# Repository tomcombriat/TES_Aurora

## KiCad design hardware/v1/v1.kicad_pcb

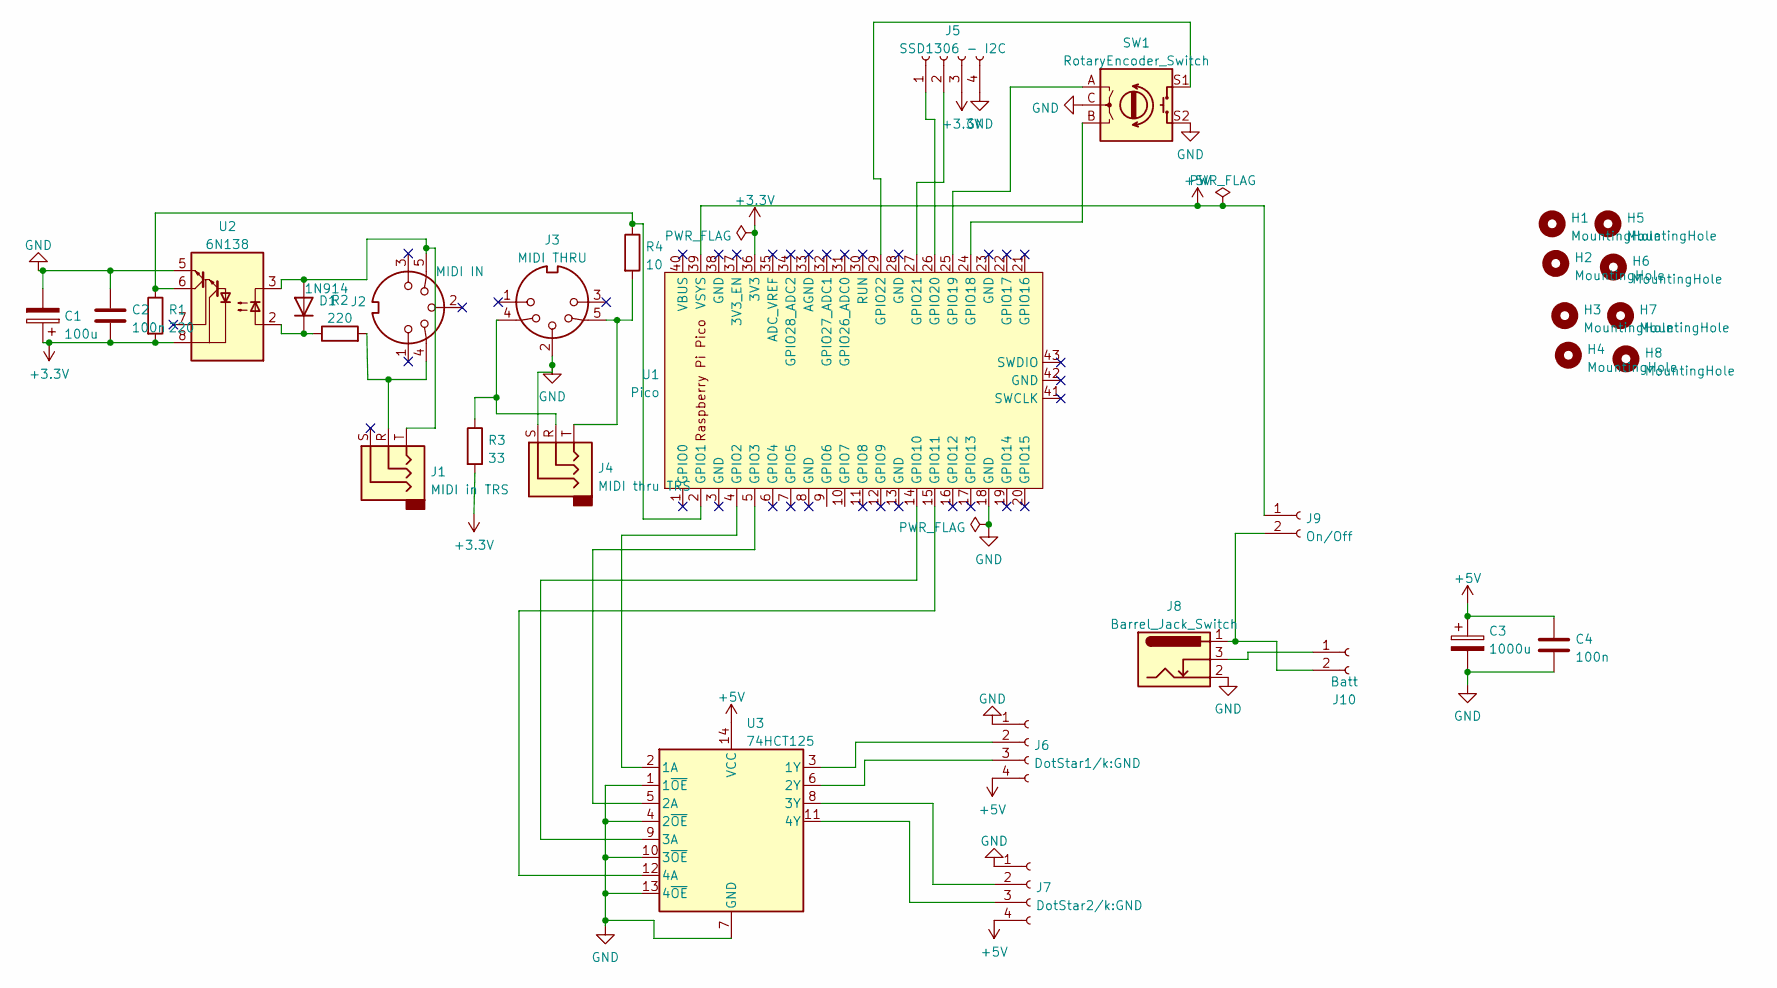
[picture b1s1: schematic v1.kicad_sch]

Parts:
C1: 100u; CP_Radial_D7.5mm_P2.50mm
C2, C4: 100n; C_Axial_L3.8mm_D2.6mm_P7.50mm_Horizontal
C3: 1000u; CP_Radial_D10.0mm_P5.00mm
D1: 1N914; D_DO-34_SOD68_P7.62mm_Horizontal
H1, H2, H3, H4, H5, H6, H7, H8: MountingHole; MountingHole_3.2mm_M3
J1: MIDI in TRS; PJ-320B
J2: MIDI IN; DS-5 MIDI_Wide
J3: MIDI THRU; DS-5 MIDI_Wide
J4: MIDI thru TRS; PJ-320B
J5: SSD1306 - I2C; JST_EH_B4B-EH-A_1x04_P2.50mm_Vertical
J6: DotStar1/k:GND; JST_PH_S4B-PH-K_1x04_P2.00mm_Horizontal
J7: DotStar2/k:GND; JST_PH_S4B-PH-K_1x04_P2.00mm_Horizontal
J8: Barrel_Jack_Switch; BarrelJack_CUI_PJ-102AH_Horizontal
J9: On/Off; JST_XH_B2B-XH-A_1x02_P2.50mm_Vertical
J10: Batt; JST_XH_B2B-XH-A_1x02_P2.50mm_Vertical
R1, R2: 220; R_Axial_DIN0207_L6.3mm_D2.5mm_P7.62mm_Horizontal
R3: 33; R_Axial_DIN0207_L6.3mm_D2.5mm_P7.62mm_Horizontal
R4: 10; R_Axial_DIN0207_L6.3mm_D2.5mm_P7.62mm_Horizontal
SW1: RotaryEncoder_Switch; RotaryEncoder_Alps_EC12E-Switch_Vertical_H20mm
U1: Pico; RPi_Pico_TH
U2: 6N138; DIP-8_W7.62mm_Socket
U3: 74HCT125; SOIC-14_3.9x8.7mm_P1.27mm

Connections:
+3.3V: C1.1, C2.2, J5.3, R1.2, R3.2, U1.36 (3V3), U2.8 (VCC)
+5V: C3.1, C4.2, J6.4, J7.4, J9.1, U1.39 (VSYS), U3.14 (VCC)
GND: C1.2, C2.1, C3.2, C4.1, J3.2, J4.S, J5.4, J6.1, J7.1, J8.2, SW1.C, SW1.S2, U1.18 (GND), U2.5 (GND), U3.1 (1~OE), U3.4 (2~OE), U3.7 (GND), U3.10 (3~OE), U3.13 (4~OE)
unnamed: D1.1 (K), R2.1, U2.2 (C1)
unnamed: D1.2 (A), J1.T, J2.5, U2.3 (C2)
unnamed: J1.R, J2.4, R2.2
unnamed: J3.4, J4.R, R3.1
unnamed: J3.5, J4.T, R4.2
unnamed: J6.2, U3.3 (1Y)
unnamed: J6.3, U3.6 (2Y)
unnamed: J7.2, U3.8 (3Y)
unnamed: J7.3, U3.11 (4Y)
unnamed: J8.3, J10.1
unnamed: J8.1, J9.2, J10.2
unnamed: R1.1, R4.1, U1.2 (GPIO1), U2.6 (VO2)
unnamed: U1.4 (GPIO2), U3.2 (1A)
unnamed: U1.5 (GPIO3), U3.5 (2A)
unnamed: U1.14 (GPIO10), U3.9 (3A)
unnamed: U1.15 (GPIO11), U3.12 (4A)
unnamed: SW1.B, U1.24 (GPIO18)
unnamed: SW1.A, U1.25 (GPIO19)
unnamed: J5.1, U1.26 (GPIO20)
unnamed: J5.2, U1.27 (GPIO21)
unnamed: SW1.S1, U1.29 (GPIO22)

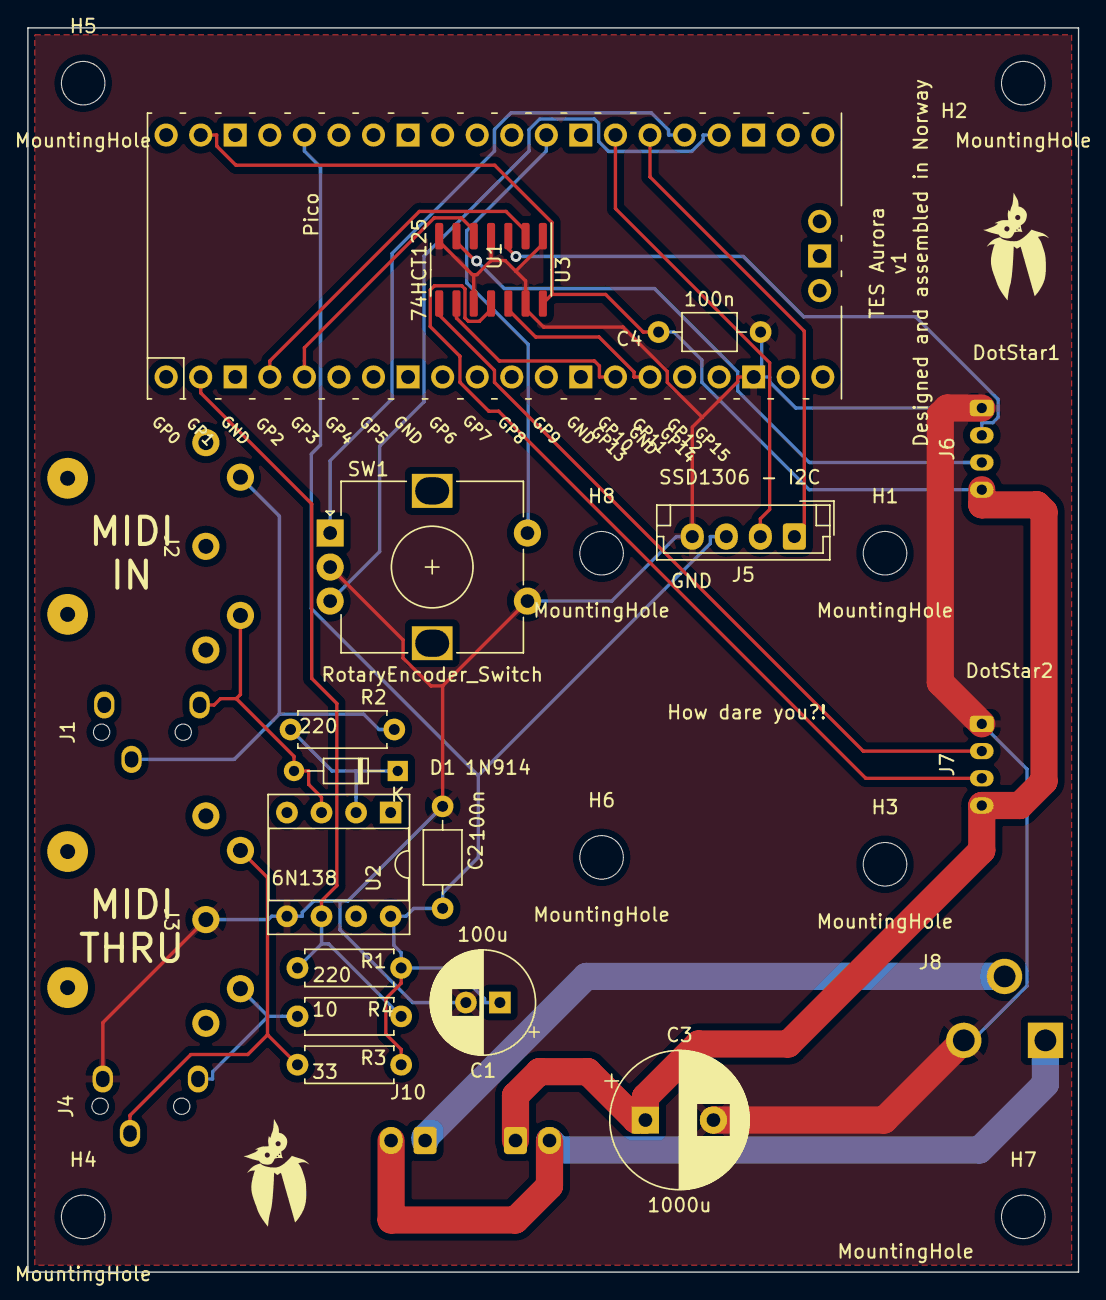
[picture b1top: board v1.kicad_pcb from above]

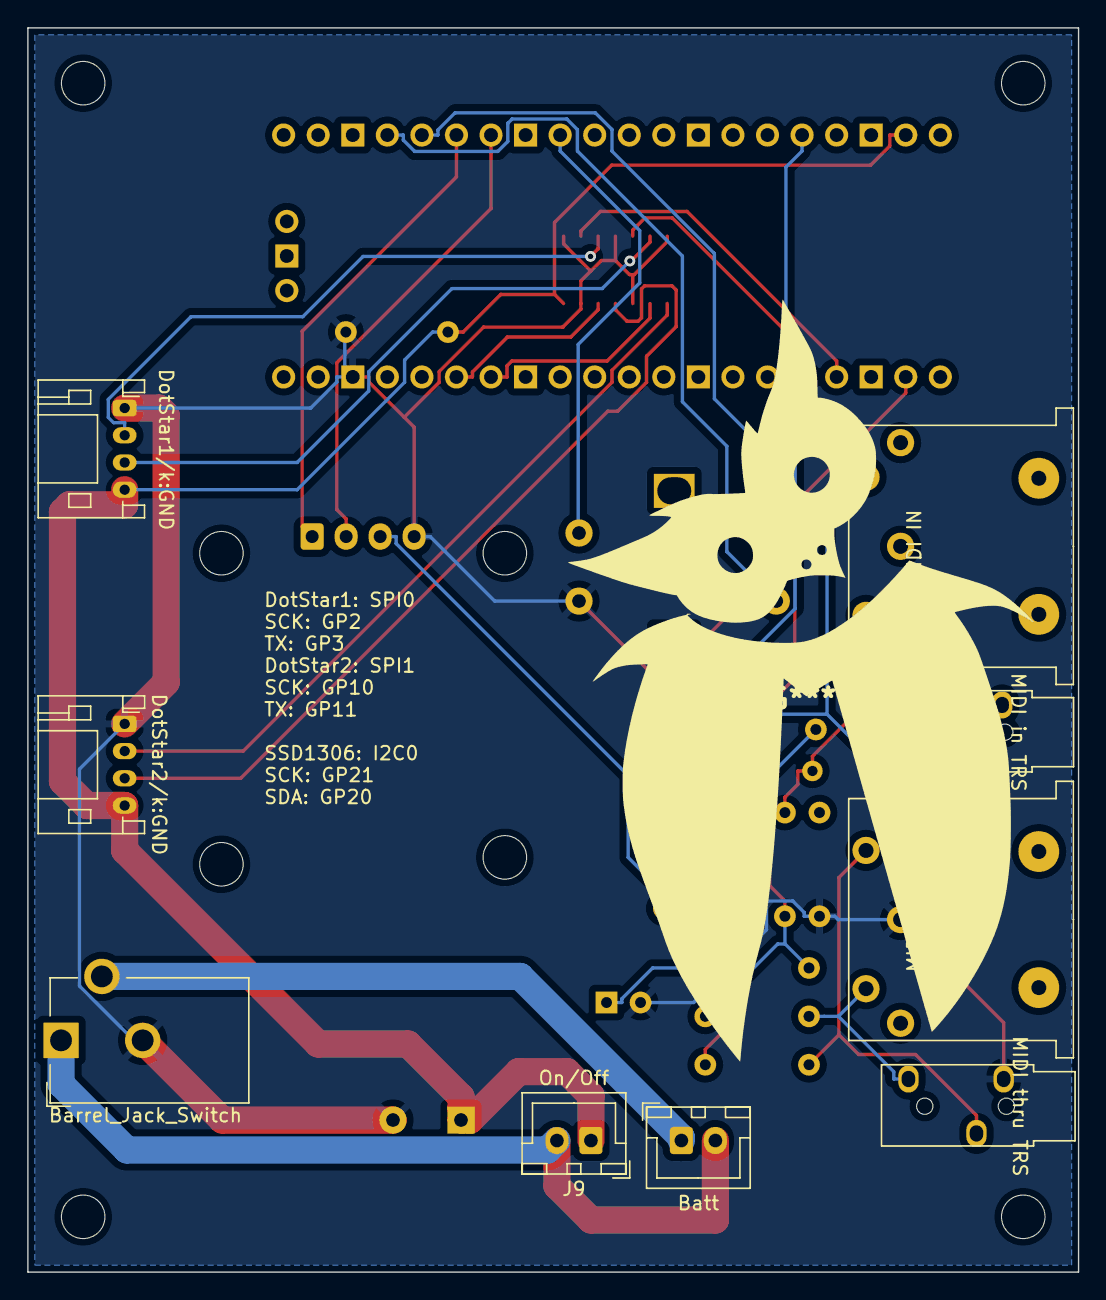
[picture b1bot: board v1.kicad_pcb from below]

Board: 2 copper layers, 77.2 x 91.4 mm, 33 parts (9 on the bottom side), 24 nets.

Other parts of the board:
G450, G2200: LOGO; owl_7x10

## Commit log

2025-04-06 Added Pico lib for kicad
2025-04-06 Started kicad proj
2025-04-06 Started schema
2025-04-08 Added additionnal components
2025-04-08 Schem and PCB
2025-04-08 Added gerber file
2025-04-08 Putting switch on bottom
2025-04-26 Started software
2025-04-26 Added color scaling
2025-04-27 MIDI sensing and wave prop
2025-04-27 Simple menu on screen
2025-04-27 Renamming
2025-04-27 Splashscreen, cleanup
2025-05-01 Use custom font
2025-05-01 Added EEPROM to store params
2025-05-01 Added folder to limit color range
2025-05-01 Added gamma32 on colors
2025-09-10 Started config file parametrizations
2025-09-10 Starting to allow mix strip types
2025-09-10 Corrected out of bound array accessing in color
2025-09-13 Renaming
2025-09-14 Added brightness and saturation in menu
2025-09-14 Comments
